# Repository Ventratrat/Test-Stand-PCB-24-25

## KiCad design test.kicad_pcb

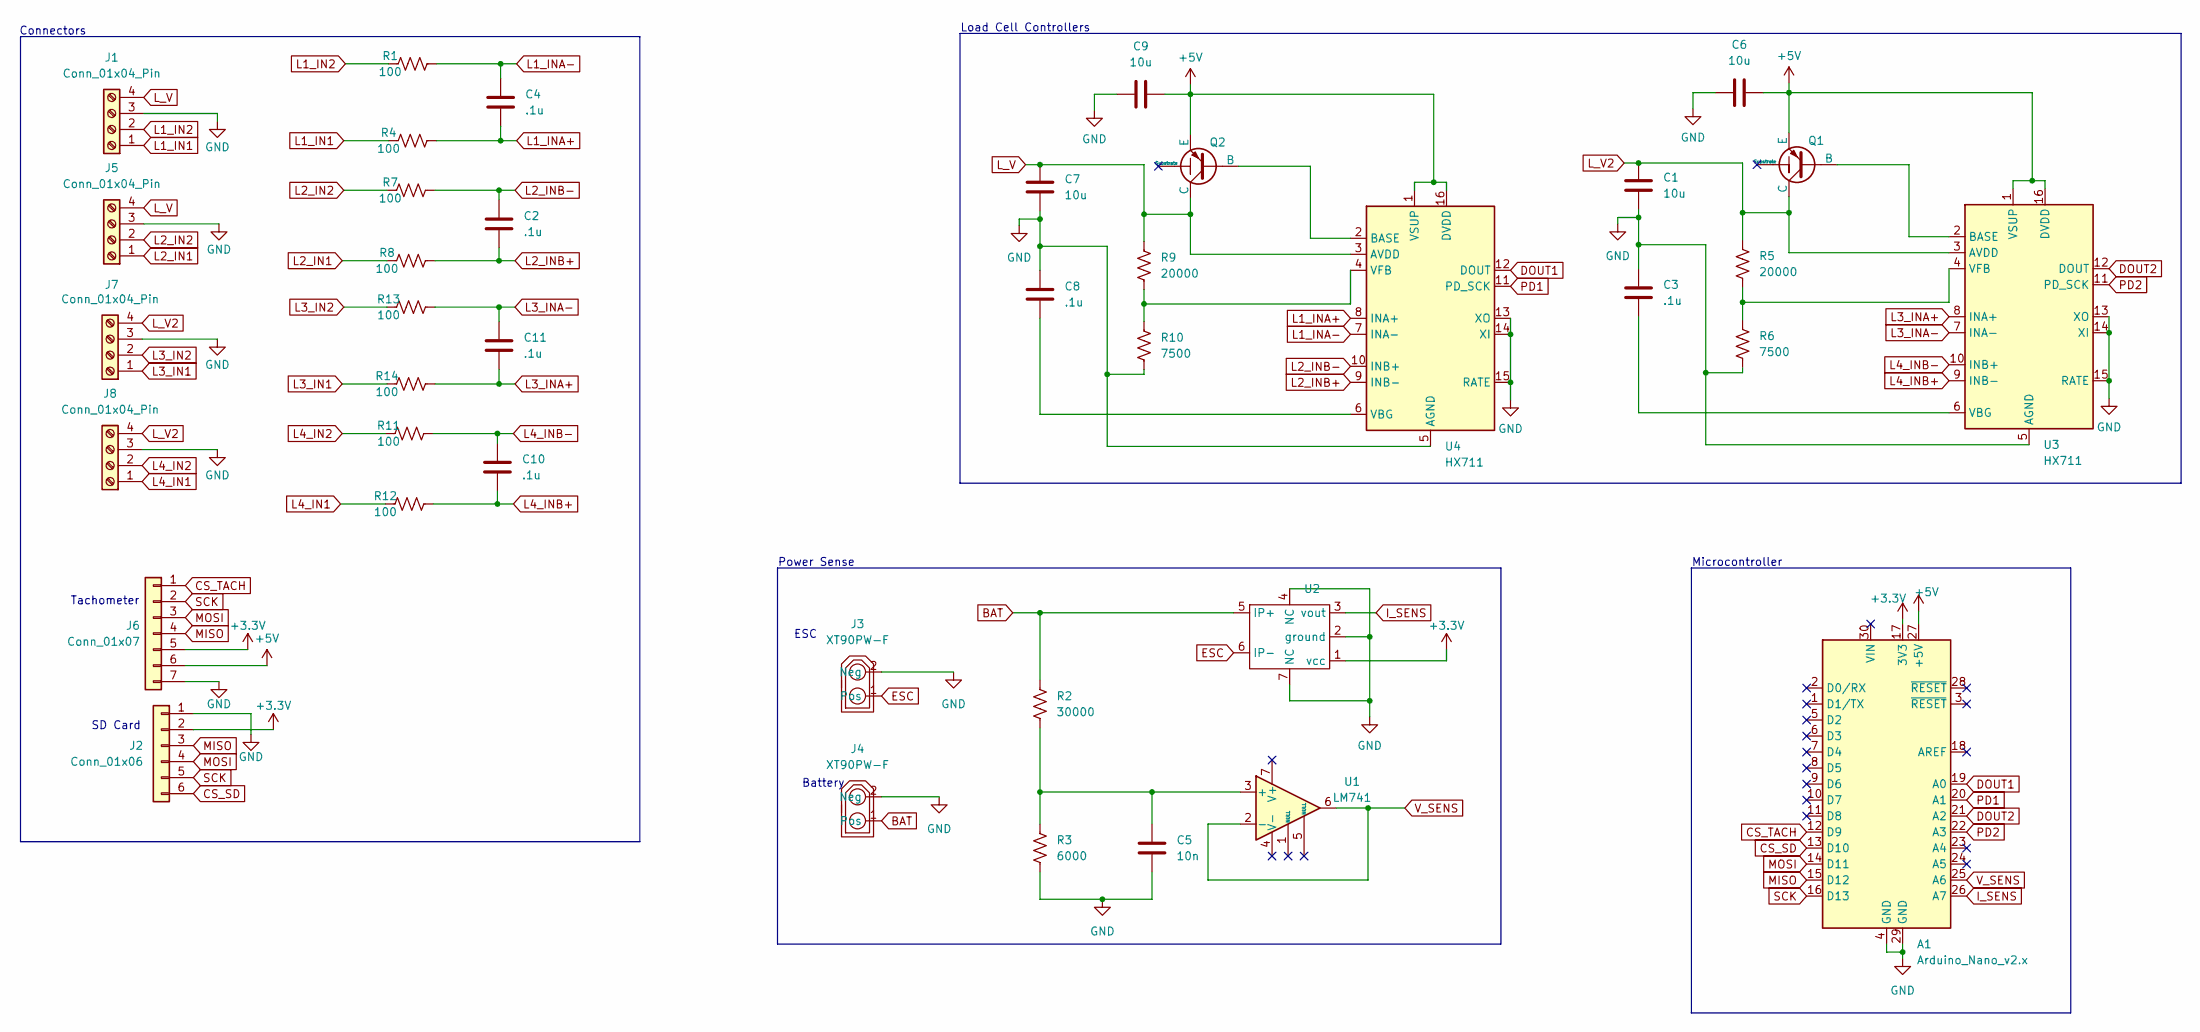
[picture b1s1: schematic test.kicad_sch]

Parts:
A1: Arduino_Nano_v2.x; Arduino_Nano
C1, C6, C7, C9: 10u; Capacitor_4mm_diam_.6mm_pin
C2, C3, C4, C8, C10, C11: .1u; Capacitor_4mm_diam_.6mm_pin
C5: 10n; Capacitor_4mm_diam_.6mm_pin
J1, J5, J7, J8: Conn_01x04_Pin; JST_EH_B4B-EH-A_1x04_P2.50mm_Vertical
J2: Conn_01x06; JST_EH_B6B-EH-A_1x06_P2.50mm_Vertical
J3, J4: XT90PW-F; XT90_-F; PARTREV V00
J6: Conn_01x07; JST_EH_B7B-EH-A_1x07_P2.50mm_Vertical
Q1, Q2: S8550 2TY DNP SOT-23 SMD 0.5A 40V; SOT-23
R1, R4, R7, R8, R11, R12, R13, R14: 100; R_1watt
R2: 30000; R_1watt
R3: 6000; R_1watt
R5, R9: 20000; R_1watt
R6, R10: 7500; R_1watt
U1: LM741; DIP-8_W7.62mm_LongPads
U2: ACS781LLRTR-100U-T
U3, U4: HX711; SOP-16_3.9x9.9mm_P1.27mm

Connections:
+3.3V: A1.17 (3V3), J2.2, J6.5, U2.1 (vcc)
+5V: A1.27 (+5V), C6.1, C9.1, J6.6, Q1.3 (E), Q2.3 (E), U3.1 (VSUP), U3.16 (DVDD), U4.1 (VSUP), U4.16 (DVDD)
BAT: J4.1 (Pos), R2.1, U2.5 (IP+)
CS_SD: A1.13 (D10), J2.6
CS_TACH: A1.12 (D9), J6.1
DOUT1: A1.19 (A0), U4.12 (DOUT)
DOUT2: A1.21 (A2), U3.12 (DOUT)
ESC: J3.1 (Pos), U2.6 (IP-)
GND: A1.4 (GND), A1.29 (GND), C1.2, C3.1, C5.2, C6.2, C7.2, C8.1, C9.2, J1.3, J2.1, J3.2 (Neg), J4.2 (Neg), J5.3, J6.7, J7.3, J8.3, R3.2, R6.2, R10.2, U2.2 (ground), U2.4 (NC), U2.7 (NC), U3.5 (AGND), U3.13 (XO), U3.14 (XI), U3.15 (RATE), U4.5 (AGND), U4.13 (XO), U4.14 (XI), U4.15 (RATE)
I_SENS: A1.26 (A7), U2.3 (vout)
L1_IN1: J1.1, R4.1
L1_IN2: J1.2, R1.1
L1_INA+: C4.2, R4.2, U4.8 (INA+)
L1_INA-: C4.1, R1.2, U4.7 (INA-)
L2_IN1: J5.1, R8.1
L2_IN2: J5.2, R7.1
L2_INB+: C2.2, R8.2, U4.9 (INB-)
L2_INB-: C2.1, R7.2, U4.10 (INB+)
L3_IN1: J7.1, R14.1
L3_IN2: J7.2, R13.1
L3_INA+: C11.2, R14.2, U3.8 (INA+)
L3_INA-: C11.1, R13.2, U3.7 (INA-)
L4_IN1: J8.1, R12.1
L4_IN2: J8.2, R11.1
L4_INB+: C10.2, R12.2, U3.9 (INB-)
L4_INB-: C10.1, R11.2, U3.10 (INB+)
L_V: C7.1, J1.4, J5.4, Q2.1 (C), R9.1, U4.3 (AVDD)
L_V2: C1.1, J7.4, J8.4, Q1.1 (C), R5.1, U3.3 (AVDD)
MISO: A1.15 (D12), J2.3, J6.4
MOSI: A1.14 (D11), J2.4, J6.3
unnamed: Q1.2 (B), U3.2 (BASE)
unnamed: Q2.2 (B), U4.2 (BASE)
unnamed: C5.1, R2.2, R3.1, U1.3 (+)
unnamed: C3.2, U3.6 (VBG)
unnamed: R5.2, R6.1, U3.4 (VFB)
unnamed: C8.2, U4.6 (VBG)
unnamed: R9.2, R10.1, U4.4 (VFB)
PD1: A1.20 (A1), U4.11 (PD_SCK)
PD2: A1.22 (A3), U3.11 (PD_SCK)
SCK: A1.16 (D13), J2.5, J6.2
V_SENS: A1.25 (A6), U1.2 (-), U1.6

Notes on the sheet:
SD Card
Tachometer
Battery
Load Cell Controllers
Connectors
ESC
Power Sense
Microcontroller

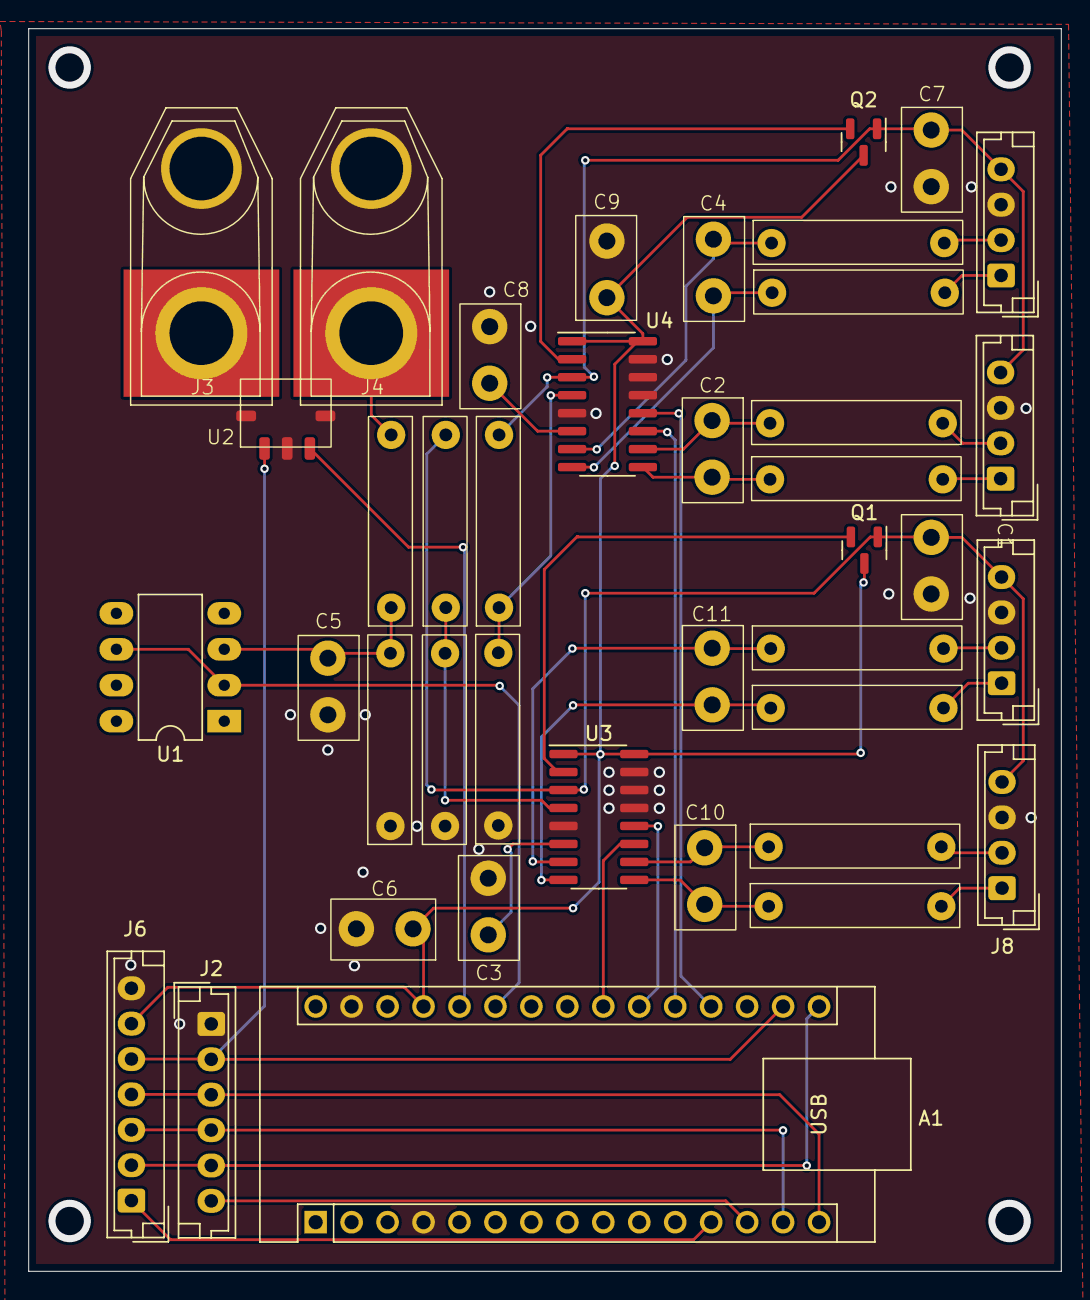
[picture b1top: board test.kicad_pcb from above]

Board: 2 copper layers, 72.9 x 87.8 mm, 40 parts (0 on the bottom side), 41 nets.

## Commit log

2025-02-26 Added new test stand files
